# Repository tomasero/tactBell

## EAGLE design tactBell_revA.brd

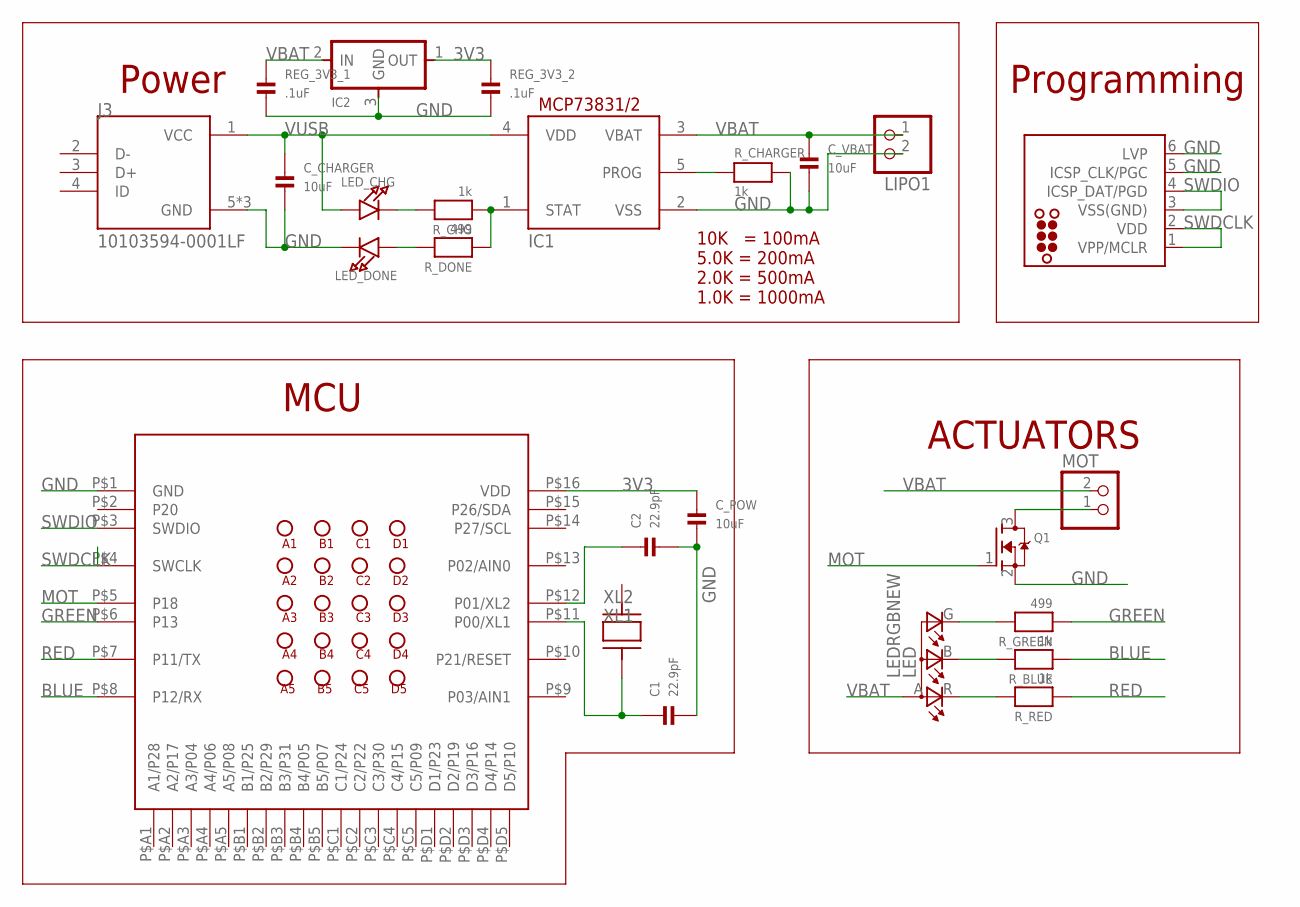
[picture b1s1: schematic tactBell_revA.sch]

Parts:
C1, C2: 22.9pF; 0603
C_CHARGER: 10uF; 0603
C_POW: 10uF; 0603
C_VBAT: 10uF; 0603
IC1: MCP73831/OT; SOT23-5L
IC2: REGULATORSOT23; SOT23
J1: TC2030-MCP-NL
J3: 10103594-0001LF; FCI_10103594-0001LF
LED: LEDRGBNEW; P-LCC-4
LED_CHG: LED0603; CHIPLED_0603
LED_DONE: LED0603; CHIPLED_0603
LIPO1: JST_2PIN-SMT-RA; JST-PH-2-SMT-RA
MOT: JST_2PIN-SMT-RA; JST-PH-2-SMT-RA
Q1: MOSFET-NREFLOW; SOT23-R
REG_3V3_1, REG_3V3_2: .1uF; 0603
R_BLUE: 1k; 0603
R_CHARGER: 1k; 0603
R_CHG: 1k; 0603
R_DONE: 499; 0603
R_GREEN: 499; 0603
R_RED: 1k; 0603
U2: BC832-V0; BC832
XL: ECX-31B

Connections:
3V3: C_POW.1, IC2.1 (OUT), REG_3V3_2.1, U2.P$16 (VDD)
B: LED.B (CBLUE), R_BLUE.2
BLUE: R_BLUE.1, U2.P$8 (P12/RX)
G: LED.G (CGREEN), R_GREEN.2
GND: C1.2, C2.2, C_CHARGER.2, C_POW.2, C_VBAT.2, IC1.2 (VSS), IC2.3 (GND), J1.5 (ICSP_CLK/PGC), J1.6 (LVP), J3.5 (GND), J3.P3 (GND), J3.P4 (GND), LED_DONE.C, LIPO1.2 (1), Q1.2 (S), REG_3V3_1.2, REG_3V3_2.2, R_CHARGER.2, U2.P$1 (GND)
GREEN: R_GREEN.1, U2.P$6 (P13)
MOT: Q1.1 (G), U2.P$5 (P18)
unnamed: LED_DONE.A, R_DONE.2
unnamed: MOT.1 (2), Q1.3 (D)
unnamed: LED_CHG.C, R_CHG.2
PROG: IC1.5 (PROG), R_CHARGER.1
R: LED.R (CRED), R_RED.2
RED: R_RED.1, U2.P$7 (P11/TX)
STAT: IC1.1 (STAT), R_CHG.1, R_DONE.1
SWDCLK: J1.1 (VPP/MCLR), J1.2 (VDD), U2.P$4 (SWCLK)
SWDIO: J1.3 (VSS(GND)), J1.4 (ICSP_DAT/PGD), U2.P$3 (SWDIO)
VBAT: C_VBAT.1, IC1.3 (VBAT), IC2.2 (IN), LED.A (A2), LIPO1.1 (2), MOT.2 (1), REG_3V3_1.1
VUSB: C_CHARGER.1, IC1.4 (VDD), J3.1 (VCC), LED_CHG.A
XL1: C1.1, U2.P$11 (P00/XL1), XL.XL1
XL2: C2.1, U2.P$12 (P01/XL2)

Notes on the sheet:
Power
10K = 100mA 5.0K = 200mA 2.0K = 500mA 1.0K = 1000mA
MCU
ACTUATORS
Programming

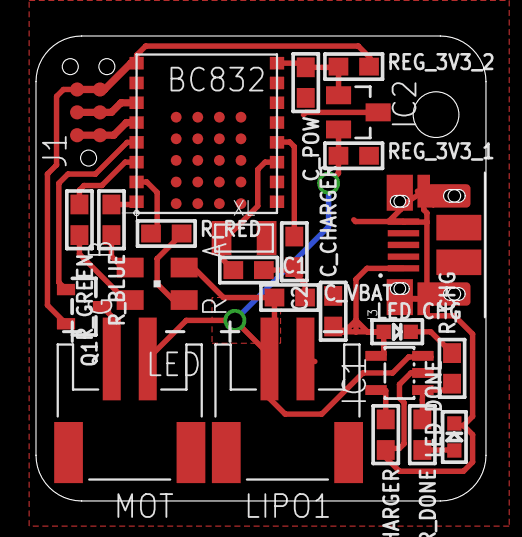
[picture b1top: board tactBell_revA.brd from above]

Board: 2 copper layers, 25.0 x 25.8 mm, 25 parts (0 on the bottom side), 20 nets.

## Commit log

2018-06-01 pa judiiii
2018-06-01 rm .lck

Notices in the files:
parts and their libraries:
microbuilder: This work is placed in the public domain, and may be freely used for commercial and non-commercial work with the following conditions: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
tag-connect: ©2009 ROFA.cz - modified and updated by Robert Darlington ‹rdarlington@gmail.com›
